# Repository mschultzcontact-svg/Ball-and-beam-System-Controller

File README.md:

# Automatisiertes Kugelbahn-System – Fokus: Balancer-Modul (Ball-on-Beam)

## Über das Projekt
Dieses Repository dokumentiert ein mechatronisches Folgeprojekt am Labor für Mechatronik und Regelungstechnik der Hochschule Osnabrück. 

Das Gesamtsystem ist als geschlossener Kreislauf konzipiert. Die Kugeln durchlaufen kontinuierlich eine dreiteilige, modular aufgebaute automatisierte Kugelbahn:

1. **Magazin & SmartSort-Modul:** Zu Beginn werden die Billardkugeln in einem Magazin gesammelt und von dort aus einzeln dem Sortierbereich zugeführt. Ein kamerabasiertes KI-System zur Bildverarbeitung erkennt die optischen Merkmale der Kugeln. Anhand dieser Klassifizierung ordnet ein 2-Achs-Handhabungsarm die Kugeln einer von drei Führungen zu.
2. **Rückführungsmodul:** Über diese Führungen rollen die Kugeln weiter zum Rückführungsmodul. Ein mechanischer Lift transportiert die Kugeln vertikal nach oben auf eine höhere Ebene, von wo aus sie eigenständig zum Vereinzeler des darauffolgenden Moduls rollen.
3. **Balancer-Modul (Ball-on-Beam):** Dieses Modul bildet den Kern und Schwerpunkt dieser Arbeit. Nach der gezielten Freigabe der Kugel durch den Vereinzeler gelangt diese auf eine bewegliche Wippe. Die Kugel wird entlang dieser 1,5 Meter langen Achse transportiert, während ein Schrittmotor den Neigungswinkel der Wippe kontinuierlich anpasst.

**Die Kernaufgabe meines Projekts:** Da dieses Kugel-auf-Balken-System inhärent instabil ist, besteht die Herausforderung darin, das System präzise zu regeln. Im Rahmen der Projektphase wird zunächst eine zentrale Steuerbox zur Signalverarbeitung und Motoransteuerung entwickelt (Teil I). Darauf aufbauend wird im Zuge der Bachelorarbeit eine robuste Regelungsstrategie mittels MATLAB-Simulation entworfen und an der realen Anlage in Betrieb genommen (Teil II), um einen dauerhaft fehlerfreien Kreislaufbetrieb zu garantieren.

---

## Repository-Struktur & Inhalt

Dieses Repository ist in funktionale Bereiche unterteilt. Nachfolgend finden Sie eine Übersicht, welche Inhalte und Daten in den jeweiligen Ordnern hinterlegt sind:

### 📁 01_Hardware
Hier befindet sich die vollständige elektrotechnische und mechanische Entwicklung der Steuerbox.
* **Datenblätter:** Technische Spezifikationen aller verwendeten Komponenten (z. B. Schrittmotor, ToF-Sensor, Mikrocontroller).
* **Schaltplan & Layout:** Die in KiCad entwickelten Platinen-Layouts (PCB), Schaltungsentwürfe sowie die Stücklisten (BOM) für die Fertigung.
* **Gehäuse:** CAD- und STL-Dateien für das Gehäuse der Steuerbox (optimiert für den 3D-Druck).

### 📁 02_Software_Firmware
Enthält den gesamten Programmcode für den realen Anlagenbetrieb sowie die Systemeinrichtung.
* **Steuerbox_Firmware:** Der produktive C/C++ Code für den Mikrocontroller, welcher im normalen Regelbetrieb die Sensorwerte einliest und den Motor ansteuert.
* **Kalibrierung:** Spezifische Testskripte zur Sensor- und Aktorkalibrierung, um Messfehler (z. B. des ToF-Sensors) vorab softwareseitig zu kompensieren.

### 📁 03_Modellierung_Simulation
Die theoretische und simulative Basis für den Reglerentwurf.
* **Modellierung:** Mathematische Herleitungen und die physikalischen Differentialgleichungen des Kugel-auf-Balken-Systems.
* **Matlab_Simulink:** `.m`-Skripte und `.slx`-Simulationsmodelle. Hier wird das System virtuell abgebildet, um Reglerstrukturen methodisch zu bedaten und eine Stabilitätsanalyse durchzuführen.
* **Messdaten:** Reale Protokolle und Schwingungsdaten aus der Anlage, die für den Abgleich zwischen Modell und Realität (Systemidentifikation) genutzt werden.

### 📁 04_Regelungsstrategie
Dokumentation und Code-Basis der untersuchten Regelungsansätze.
* Hier sind die verschiedenen evaluierten Regelungskonzepte hinterlegt (z. B. klassischer PID-Regler, Kaskadenregelung oder Zustandsregler). Es wird dokumentiert, wie die Strategien auf Störeinflüsse reagieren (z. B. beim transienten Eintritt der Kugel in das Modul) und welche Strategie die beste Stabilität liefert.

### 📁 05_Dokumentation
Begleitmaterialien und schriftliche Ausarbeitungen.
* Enthält den schriftlichen Projektbericht (Teil I: Steuerbox-Entwicklung & Teil II: Bachelorarbeit-Konzept inklusive Pflichtenheft und Projektplanung) sowie wichtige Systemgrafiken und Schaubilder.

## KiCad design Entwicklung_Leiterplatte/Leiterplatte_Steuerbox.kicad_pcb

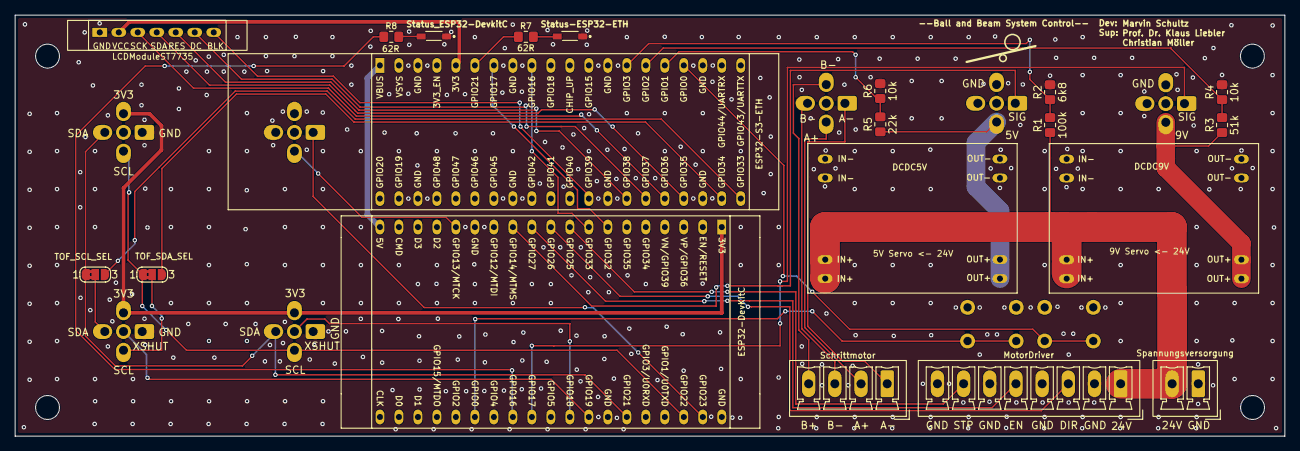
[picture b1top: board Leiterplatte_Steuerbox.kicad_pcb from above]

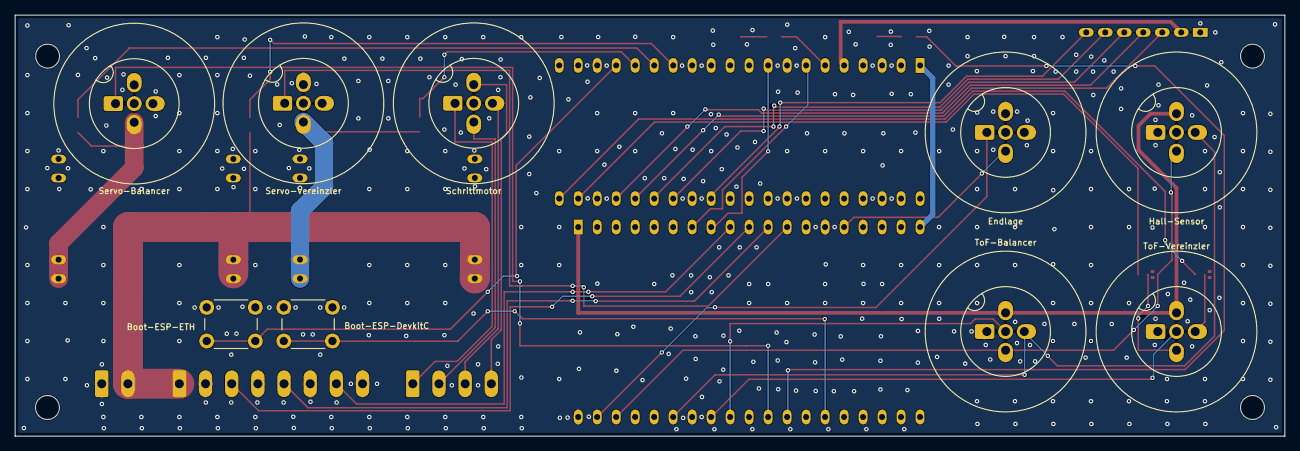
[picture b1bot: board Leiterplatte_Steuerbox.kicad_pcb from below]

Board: 2 copper layers, 169.8 x 56.3 mm, 33 parts (9 on the bottom side), 42 nets.

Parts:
Boot_ESP_DevkitC1: Boot-ESP-DevkitC; SW_PUSH_6mm_H13mm
Boot_ESP_ETH1: Boot-ESP-ETH; SW_PUSH_6mm_H13mm
DCDC-24V5V1: DCDC-24V5V; DCDC
DCDC-24V9V1: DCDC-24V9V; DCDC
Endlage1: Endlage; Liebler_Connector
H1, H2, H3, H4: MountingHole; MountingHole_3.2mm_M3
Hall-Sensor1: Hall-Sensor; Liebler_Connector
JP1: TOF_SDA_SEL; SolderJumper-3_P1.3mm_Bridged2Bar12_RoundedPad1.0x1.5mm_Num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
JP2: TOF_SCL_SEL; SolderJumper-3_P1.3mm_Bridged2Bar12_RoundedPad1.0x1.5mm_Num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
LCDModuleST7735: Conn_01x07_Pin; TFT-Display
LED1: Status-ESP32-ETH; LSY876P2S11
LED2: Status_ESP32-DevkitC; LSY876P2S11
MotorDriver1: MotorDriver; PhoenixContact_MCV_1,5_8-G-3.5_1x08_P3.50mm_Vertical
R1: 100k; R_0805_2012Metric_Pad1.20x1.40mm_HandSolder
R2: 6k8; R_0805_2012Metric_Pad1.20x1.40mm_HandSolder
R3: 51k; R_0805_2012Metric_Pad1.20x1.40mm_HandSolder
R4, R6: 10k; R_0805_2012Metric_Pad1.20x1.40mm_HandSolder
R5: 22k; R_0805_2012Metric_Pad1.20x1.40mm_HandSolder
R7, R8: 62R; R_0805_2012Metric_Pad1.20x1.40mm_HandSolder
Schrittmotor1: Schrittmotor; PhoenixContact_MCV_1,5_4-G-3.5_1x04_P3.50mm_Vertical
Schrittmotor2: Schrittmotor; Liebler_Connector
ServoBalancer1: Servo-Balancer; Liebler_Connector
ServoVereinzler1: Servo-Vereinzler; Liebler_Connector
Spannungsversorgung1: Spannungsversorgung; PhoenixContact_MCV_1,5_2-G-3.5_1x02_P3.50mm_Vertical
ToF-Vereinzler1: ToF-Vereinzler; Liebler_Connector
ToFBalancer1: ToF-Balancer; Liebler_Connector
U1: ESP32-S3-ETH
U2: ESP32-DevKitC

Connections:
+3V3_ESP32DevKitC: Hall-Sensor1.2, ToF-Vereinzler1.2, ToFBalancer1.2, U2.1 (3V3)
+3V3_ESP32ETH: LCDModuleST7735.2, U1.36 (3V3)
+5V: DCDC-24V5V1.7 (OUT+), DCDC-24V5V1.8 (OUT+), R5.1, ServoVereinzler1.4
+9V: DCDC-24V9V1.7 (OUT+), DCDC-24V9V1.8 (OUT+), R3.1, ServoBalancer1.4
+24V: DCDC-24V5V1.3 (IN+), DCDC-24V5V1.4 (IN+), DCDC-24V9V1.3 (IN+), DCDC-24V9V1.4 (IN+), MotorDriver1.1, R1.1, Spannungsversorgung1.2
/Boot_G0: Boot_ESP_DevkitC1.2, U2.25 (*GPIO0/BOOT/ADC2_CH1)
/ESP1_RX_ESP2_TX: U1.34 (GPIO17), U2.7 (32K_XP/GPIO32/ADC1_CH4)
/ESP1_TX_ESP2_RX: U1.32 (GPIO16), U2.8 (32K_XN/GPIO33/ADC1_CH5)
/ETH_Boot_G0: Boot_ESP_ETH1.2, U1.24 (GPIO0)
/Endlage_Kugelabgabe: Endlage1.1, U2.37 (GPIO23)
/Endlage_Kugelaufnahme: Endlage1.4, U2.15 (MTCK/GPIO13/ADC2_CH4)
/SCL_ESP32DevKitC: Hall-Sensor1.4, JP1.1 (A), ToFBalancer1.4, U2.36 (GPIO22)
/SCL_ESP32ETH: JP1.3 (B), U1.19 (GPIO34)
/SDA_ESP32DevKitC: Hall-Sensor1.3, JP2.1 (A), ToFBalancer1.3, U2.33 (GPIO21)
/SDA_ESP32ETH: JP2.3 (B), U1.20 (GPIO33)
/STP_DIR: MotorDriver1.3, U2.10 (DAC_2/ADC2_CH9/GPIO26)
/STP_EN: MotorDriver1.5, U2.11 (ADC2_CH7/GPIO27)
/STP_STEP: MotorDriver1.7, U2.9 (DAC_1/ADC2_CH8/GPIO25)
/Schrittmotor_A+: Schrittmotor1.2, Schrittmotor2.4
/Schrittmotor_A-: Schrittmotor1.1, Schrittmotor2.1
/Schrittmotor_B+: Schrittmotor1.4, Schrittmotor2.2
/Schrittmotor_B-: Schrittmotor1.3, Schrittmotor2.3
/Servo_Balancer_TX: ServoBalancer1.1, U2.28 (GPIO17)
/Servo_Vereinzler: ServoVereinzler1.1, U2.12 (MTMS/GPIO14/ADC2_CH6)
/TFT_BLK: LCDModuleST7735.7, U1.12 (GPIO39)
/TFT_DC: LCDModuleST7735.6, U1.15 (GPIO37)
/TFT_RES: LCDModuleST7735.5, U1.14 (GPIO38)
/TFT_SCK: LCDModuleST7735.3, U1.16 (GPIO36)
/TFT_SDA: LCDModuleST7735.4, U1.17 (GPIO35)
/ToF_Balancer_XSHUT: ToFBalancer1.5, U2.30 (GPIO18)
/ToF_Vereinzler_SCL: JP1.2 (C), ToF-Vereinzler1.4
/ToF_Vereinzler_SDA: JP2.2 (C), ToF-Vereinzler1.3
/ToF_Vereinzler_XSHUT: ToF-Vereinzler1.5, U2.31 (GPIO19)
/Überw_5V: R5.2, R6.1, U1.25 (GPIO1)
/Überw_9V: R3.2, R4.1, U1.26 (GPIO2)
/Überw_24V: R1.2, R2.1, U1.27 (GPIO3)
GND: Boot_ESP_DevkitC1.1, Boot_ESP_ETH1.1, DCDC-24V5V1.1 (IN-), DCDC-24V5V1.2 (IN-), DCDC-24V5V1.5 (OUT-), DCDC-24V5V1.6 (OUT-), DCDC-24V9V1.1 (IN-), DCDC-24V9V1.2 (IN-), DCDC-24V9V1.5 (OUT-), DCDC-24V9V1.6 (OUT-), Endlage1.2, Endlage1.3, Hall-Sensor1.1, LCDModuleST7735.1, LED1.1 (K), LED2.1 (K), MotorDriver1.2, MotorDriver1.4, MotorDriver1.6, MotorDriver1.8, R2.2, R4.2, R6.2, ServoBalancer1.3, ServoVereinzler1.2, Spannungsversorgung1.1, ToF-Vereinzler1.1, ToFBalancer1.1, U1.3 (GND), U1.8 (GND), U1.13 (GND), U1.18 (GND), U1.23 (GND), U1.28 (GND), U1.33 (GND), U1.38 (GND), U2.14 (GND), U2.32 (GND), U2.38 (GND)
unnamed: LED1.2 (A), R7.1
unnamed: LED2.2 (A), R8.1
unnamed: R7.2, U1.35 (GPIO21)
unnamed: U1.40 (VBUS), U2.19 (5V)
unnamed: R8.2, U2.27 (GPIO16)

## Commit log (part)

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2026-06-24 Rename esp32_devkitc_v4_sch.pdf to esp32_devkitc_Schematics.pdf
